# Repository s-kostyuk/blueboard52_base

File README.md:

# blueboard52_base

This repostiory contains sources for the nRF52832-based board design that can be integrated into various projects.

For example, it has bottom headers and may be stacked on a base board like this: [ValentiWorkLearning/GradWork](https://github.com/ValentiWorkLearning/GradWork). Or may be used as autonomously-powered wireless sensor node with CR2302 battery slot on the back. Or for other purposes as you like.

If needed, the female headers may be soldered on top of the board for rapid prototyping, by analogy with Arduino Uno boards. But you may need to move pin annotations to the top header in this case.

And finally, here is the board. The top and bottom view images are below. Manufacture with blue soldermask and white LED for the best results :)

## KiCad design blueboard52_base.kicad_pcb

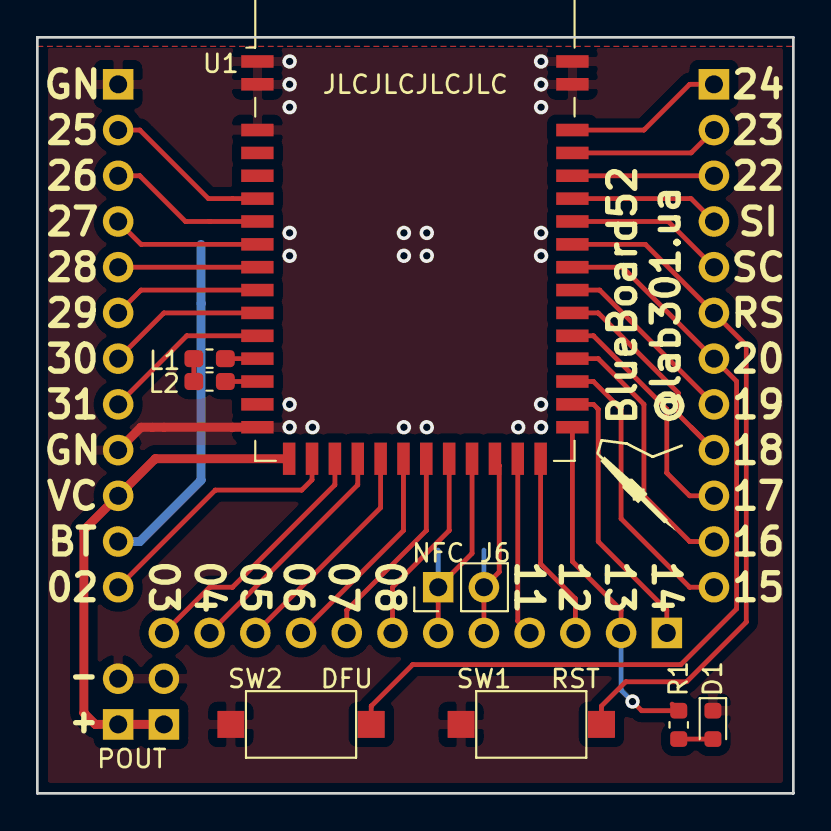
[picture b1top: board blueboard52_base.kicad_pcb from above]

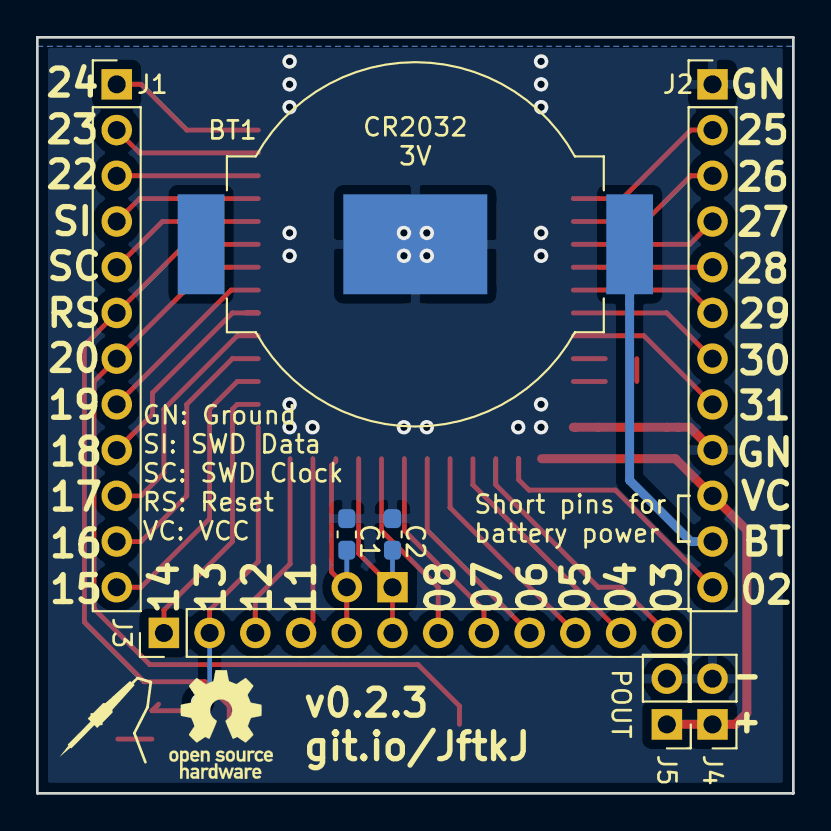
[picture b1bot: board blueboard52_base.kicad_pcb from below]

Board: 2 copper layers, 42.0 x 42.0 mm, 18 parts (9 on the bottom side), 39 nets.

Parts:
BT1: Battery_Cell; BatteryHolder_MPD_BC2003_1x2032
C1, C2: 300pf; C_0603_1608Metric_Pad1.05x0.95mm_HandSolder
D1: RED; LED_0603_1608Metric
J1: Conn_East; PinHeader_1x12_P2.54mm_Vertical
J2: Conn_West; PinHeader_1x12_P2.54mm_Vertical
J3: Conn_South; PinHeader_1x12_P2.54mm_Vertical
J4, J5: POUT; PinHeader_1x02_P2.54mm_Vertical
J6: NFC; PinHeader_1x02_P2.54mm_Vertical
L1: 15nH; L_0603_1608Metric_Pad1.05x0.95mm_HandSolder
L2: 10uH; L_0603_1608Metric_Pad1.05x0.95mm_HandSolder
R1: 1K; R_0603_1608Metric
SW1: RST; SW_SPST_CK_RS282G05A3
SW2: DFU; SW_SPST_CK_RS282G05A3
U1: E73-2G4M04S-52832; E73-2G4M04S
svg2mod, svg2mod#2: G***; lab301i_logo

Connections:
+BATT: BT1.1, J2.11
/DFU: J1.7, SW2.1, U1.35
/P0.2: J2.12, U1.17
/P0.3: J3.12, U1.18
/P0.4: J3.11, U1.19
/P0.5: J3.10, U1.20
/P0.6: J3.9, U1.21
/P0.7: J3.8, U1.22
/P0.8: J3.7, U1.23
/P0.9: C2.1, J3.6, J6.1, U1.24
/P0.10: C1.2, J3.5, J6.2, U1.25
/P0.11: J3.4, U1.26
/P0.12: J3.3, U1.27
/P0.14: J3.1, U1.29
/P0.15: J1.12, U1.30
/P0.16: J1.11, U1.31
/P0.17: J1.10, U1.32
/P0.18: J1.9, U1.33
/P0.19: J1.8, U1.34
/P0.22: J1.3, U1.39
/P0.23: J1.2, U1.40
/P0.24: J1.1, U1.41
/P0.25: J2.2, U1.5
/P0.26: J2.3, U1.6
/P0.27: J2.4, U1.7
/P0.28: J2.5, U1.8
/P0.29: J2.6, U1.9
/P0.30: J2.7, U1.10
/P0.31: J2.8, U1.11
/SWDCLK: J1.5, U1.37
/SWDIO: J1.4, U1.38
/USER_LED1: J3.2, R1.1, U1.28
/nRST: J1.6, SW1.2, U1.36
GND: BT1.2, C1.1, C2.2, D1.1, J2.1, J2.9, J4.2, J5.2, SW1.1, SW2.2, U1.0, U1.1, U1.2, U1.15, U1.42, U1.43
unnamed: D1.2, R1.2
unnamed: L1.1, U1.12
unnamed: L1.2, L2.1
unnamed: L2.2, U1.13
VCC: J2.10, J4.1, J5.1, U1.16

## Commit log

2019-10-27 Added initial version of the BlueBoard52 design.
    - Routed the base board with nRF52 module
    - Routed DFU and RESET buttons
    - Routed one user LED on P0.13
    - Added power source selection pins
    - Added CR2032 battery holder for autonomous operation
    - Added annotation for all the pins and headers
2019-10-27 Added pictures and a PDF file with schematic
    ...to illustrate the board without needing a computer with KiCAD installed.
2019-10-27 Added some base information to the readme file
2019-11-02 Added version info to the board
2019-11-03 Added some base inforamation to the README file
2020-03-21 New version of the board - v0.2.0
    - Added a separate NFC header
    - Created a solid (almost) ground plane on the bottom
    - Added silkscreen markings to the top layer
    - Removed a bulky power source selector - either a BAT jumper or
    external power source can now be used to power the board
2020-03-21 Small fixes - v0.2.1
    - Restored a grid of vias between ground planes
    - Updated version info in schematic
    - Other small fixes
2020-03-21 Updated docs for version v0.2.1
2020-03-22 Updated docs and pictures for the v0.2.2
2020-03-22 v0.2.2 - Visual cleanup
    - Reviewed ground planes once again.
    Return current from external connector now flows on the top layer
    and from the battery - on the bottom copper layer.
    - Listed main acronims for board pins
    - Added a note for Battery-VCC jumper
    - Other small changes
2020-04-11 Specified location for manufacturing number
2020-04-25 v0.2.3 - Power out connection and dimentions
    - Moved power out connector to be friendly with 2.54mm breadboard grid
    - Updated annotation for power out connector
    - For power **input** you are still supposed to use VC and GN pins
    (it should not matter much, just connections are shorter)
    - Updated PCB dimentions: now it's pretty 42x42mm square,
    no fractional dimentsions anymore
2020-04-25 Updated docs and pictures for the v0.2.3
